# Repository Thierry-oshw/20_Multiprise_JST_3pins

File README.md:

# 20_Multiprise_JST_3pins
 Multiprise JST XH 3 points

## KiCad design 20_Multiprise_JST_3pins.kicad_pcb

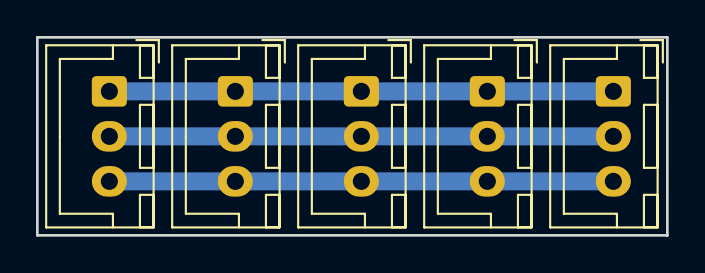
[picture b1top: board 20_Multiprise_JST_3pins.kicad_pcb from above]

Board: 2 copper layers, 35.0 x 11.0 mm, 5 parts (0 on the bottom side), 3 nets.

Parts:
J1, J2, J3, J4, J5: Conn_01x03; JST_XH_B3B-XH-A_1x03_P2.50mm_Vertical

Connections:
pin1: J1.1, J2.1, J3.1, J4.1, J5.1
pin2: J1.2, J2.2, J3.2, J4.2, J5.2
pin3: J1.3, J2.3, J3.3, J4.3, J5.3

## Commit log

2021-06-10 schéma + routage
2021-06-10 ajout licence cern
2021-07-26 maj split librairies
2023-05-02 chgt nom fichier licence
